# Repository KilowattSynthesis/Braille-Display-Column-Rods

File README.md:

# Braille-Display-Column-Rods
Braille display POC using tiny stepper motors to drive columns of the display

**Type 4 Braille Display**

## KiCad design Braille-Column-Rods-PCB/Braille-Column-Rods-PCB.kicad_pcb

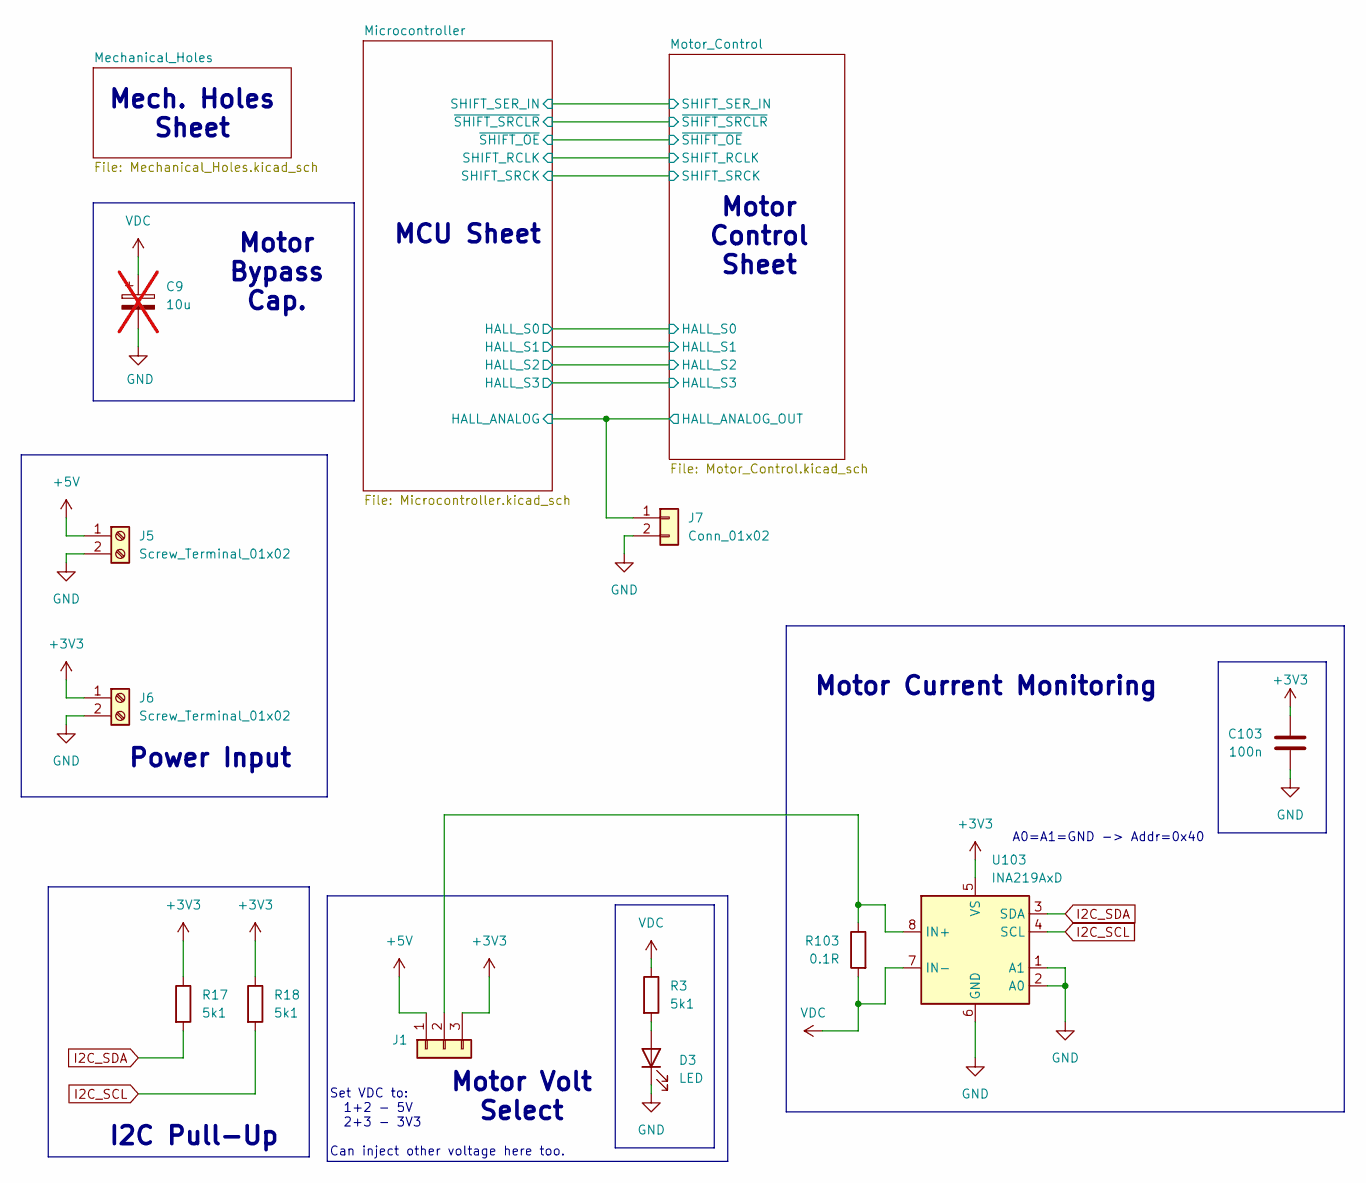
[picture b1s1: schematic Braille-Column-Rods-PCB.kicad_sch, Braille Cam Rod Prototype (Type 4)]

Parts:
C9: 10u; CP_Radial_D6.3mm_P2.50mm; not fitted
C103: 100n; C_0603_1608Metric_Pad1.08x0.95mm_HandSolder
D3: LED; LED_0603_1608Metric_Pad1.05x0.95mm_HandSolder
J1: Conn_01x03; PinHeader_1x03_P2.54mm_Vertical
J5, J6: Screw_Terminal_01x02; TerminalBlock_bornier-2_P5.08mm
J7: Conn_01x02; PinHeader_1x02_P2.54mm_Vertical
R3, R17, R18: 5k1; R_0603_1608Metric_Pad0.98x0.95mm_HandSolder
R103: 0.1R; R_1206_3216Metric_Pad1.30x1.75mm_HandSolder
U103: INA219AxD; SOIC-8_3.9x4.9mm_P1.27mm

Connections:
+3V3: C103.1, J1.3, J6.1, R17.1, R18.1, U103.5 (VS); also elsewhere on the board
+5V: J1.1, J5.1; also elsewhere on the board
/Microcontroller/HALL_ANALOG: J7.1; also elsewhere on the board
GND: C9.2, C103.2, D3.1 (K), J5.2, J6.2, J7.2, U103.1 (A1), U103.2 (A0), U103.6 (GND); also elsewhere on the board
I2C_SCL: R18.2, U103.4 (SCL); also elsewhere on the board
I2C_SDA: R17.2, U103.3 (SDA); also elsewhere on the board
unnamed: D3.2 (A), R3.2
unnamed: J1.2, R103.1, U103.8 (IN+)
VDC: C9.1, R3.1, R103.2, U103.7 (IN-); also elsewhere on the board

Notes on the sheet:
Motor Volt Select
Motor Bypass Cap.
A0=A1=GND -> Addr=0x40
Motor Current Monitoring
Mech. Holes Sheet
I2C Pull-Up
Set VDC to: 1+2 - 5V 2+3 - 3V3 Can inject other voltage here too.
MCU Sheet
Power Input
Motor Control Sheet

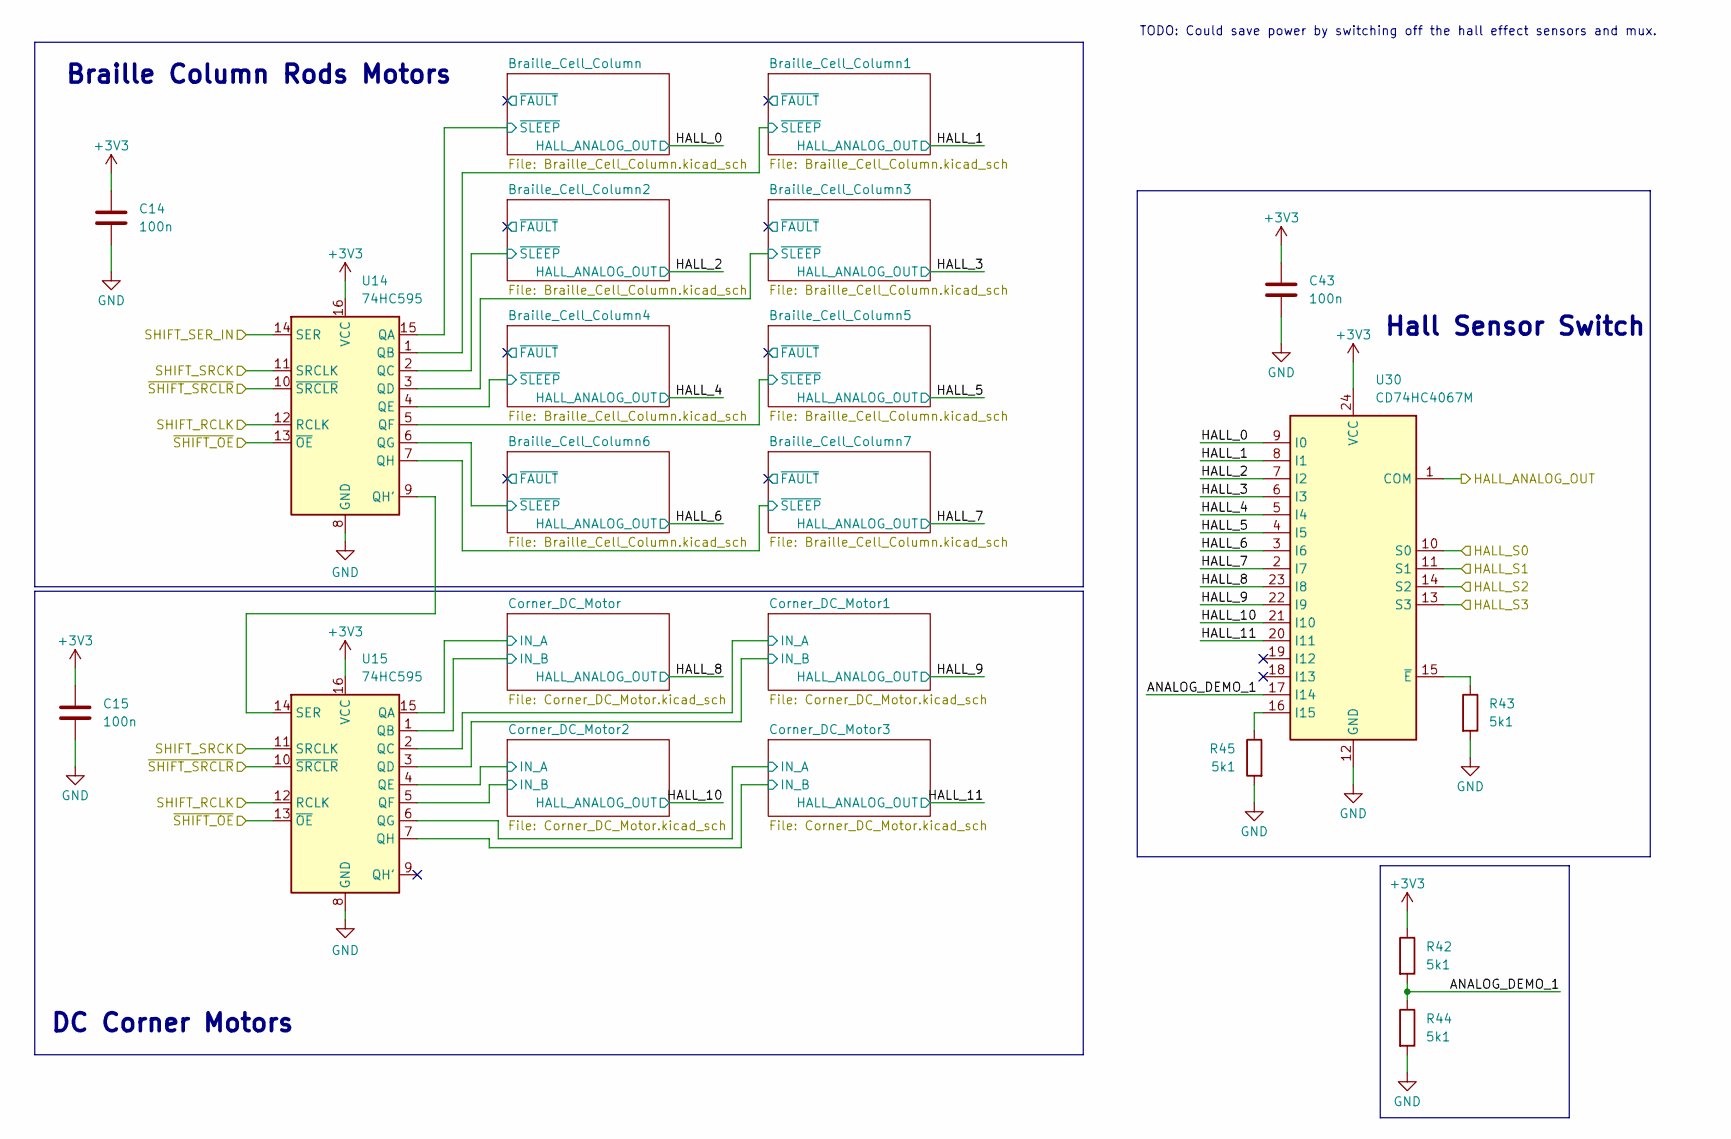
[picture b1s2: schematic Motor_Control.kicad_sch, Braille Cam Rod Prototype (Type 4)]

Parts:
C14, C15, C43: 100n; C_0603_1608Metric_Pad1.08x0.95mm_HandSolder
R42, R43, R44, R45: 5k1; R_0603_1608Metric_Pad0.98x0.95mm_HandSolder
U14, U15: 74HC595; SOP-16_3.9x9.9mm_P1.27mm; LCSC C5947
U30: CD74HC4067M; SOIC-24W_7.5x15.4mm_P1.27mm

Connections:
+3V3: C14.1, C15.1, C43.1, R42.1, U14.16 (VCC), U15.16 (VCC), U30.24 (VCC); also elsewhere on the board
/Microcontroller/HALL_ANALOG: U30.1 (COM); also elsewhere on the board
/Microcontroller/HALL_S0: U30.10 (S0); also elsewhere on the board
/Microcontroller/HALL_S1: U30.11 (S1); also elsewhere on the board
/Microcontroller/HALL_S2: U30.14 (S2); also elsewhere on the board
/Microcontroller/HALL_S3: U30.13 (S3); also elsewhere on the board
/Microcontroller/SHIFT_RCLK: U14.12 (RCLK), U15.12 (RCLK); also elsewhere on the board
/Microcontroller/SHIFT_SER_IN: U14.14 (SER); also elsewhere on the board
/Microcontroller/SHIFT_SRCK: U14.11 (SRCLK), U15.11 (SRCLK); also elsewhere on the board
/Microcontroller/~SHIFT_OE: U14.13 (~OE), U15.13 (~OE); also elsewhere on the board
/Microcontroller/~SHIFT_SRCLR: U14.10 (~SRCLR), U15.10 (~SRCLR); also elsewhere on the board
/Motor_Control/ANALOG_DEMO_1: R42.2, R44.1, U30.17 (I14)
/Motor_Control/Braille_Cell_Column1/~SLEEP: U14.1 (QB); also elsewhere on the board
/Motor_Control/Braille_Cell_Column2/~SLEEP: U14.2 (QC); also elsewhere on the board
/Motor_Control/Braille_Cell_Column3/~SLEEP: U14.3 (QD); also elsewhere on the board
/Motor_Control/Braille_Cell_Column4/~SLEEP: U14.4 (QE); also elsewhere on the board
/Motor_Control/Braille_Cell_Column5/~SLEEP: U14.5 (QF); also elsewhere on the board
/Motor_Control/Braille_Cell_Column6/~SLEEP: U14.6 (QG); also elsewhere on the board
/Motor_Control/Braille_Cell_Column7/~SLEEP: U14.7 (QH); also elsewhere on the board
/Motor_Control/Braille_Cell_Column/~SLEEP: U14.15 (QA); also elsewhere on the board
/Motor_Control/Corner_DC_Motor1/IN_A: U15.2 (QC); also elsewhere on the board
/Motor_Control/Corner_DC_Motor1/IN_B: U15.3 (QD); also elsewhere on the board
/Motor_Control/Corner_DC_Motor2/IN_A: U15.4 (QE); also elsewhere on the board
/Motor_Control/Corner_DC_Motor2/IN_B: U15.5 (QF); also elsewhere on the board
/Motor_Control/Corner_DC_Motor3/IN_A: U15.6 (QG); also elsewhere on the board
/Motor_Control/Corner_DC_Motor3/IN_B: U15.7 (QH); also elsewhere on the board
/Motor_Control/Corner_DC_Motor/IN_A: U15.15 (QA); also elsewhere on the board
/Motor_Control/Corner_DC_Motor/IN_B: U15.1 (QB); also elsewhere on the board
/Motor_Control/HALL_0: U30.9 (I0); also elsewhere on the board
/Motor_Control/HALL_1: U30.8 (I1); also elsewhere on the board
/Motor_Control/HALL_2: U30.7 (I2); also elsewhere on the board
/Motor_Control/HALL_3: U30.6 (I3); also elsewhere on the board
/Motor_Control/HALL_4: U30.5 (I4); also elsewhere on the board
/Motor_Control/HALL_5: U30.4 (I5); also elsewhere on the board
/Motor_Control/HALL_6: U30.3 (I6); also elsewhere on the board
/Motor_Control/HALL_7: U30.2 (I7); also elsewhere on the board
/Motor_Control/HALL_8: U30.23 (I8); also elsewhere on the board
/Motor_Control/HALL_9: U30.22 (I9); also elsewhere on the board
/Motor_Control/HALL_10: U30.21 (I10); also elsewhere on the board
/Motor_Control/HALL_11: U30.20 (I11); also elsewhere on the board
GND: C14.2, C15.2, C43.2, R43.2, R44.2, R45.2, U14.8 (GND), U15.8 (GND), U30.12 (GND); also elsewhere on the board
unnamed: U14.9 (QH'), U15.14 (SER)
unnamed: R45.1, U30.16 (I15)
unnamed: R43.1, U30.15 (~E)

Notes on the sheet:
Hall Sensor Switch
Braille Column Rods Motors
TODO: Could save power by switching off the hall effect sensors and mux.
DC Corner Motors

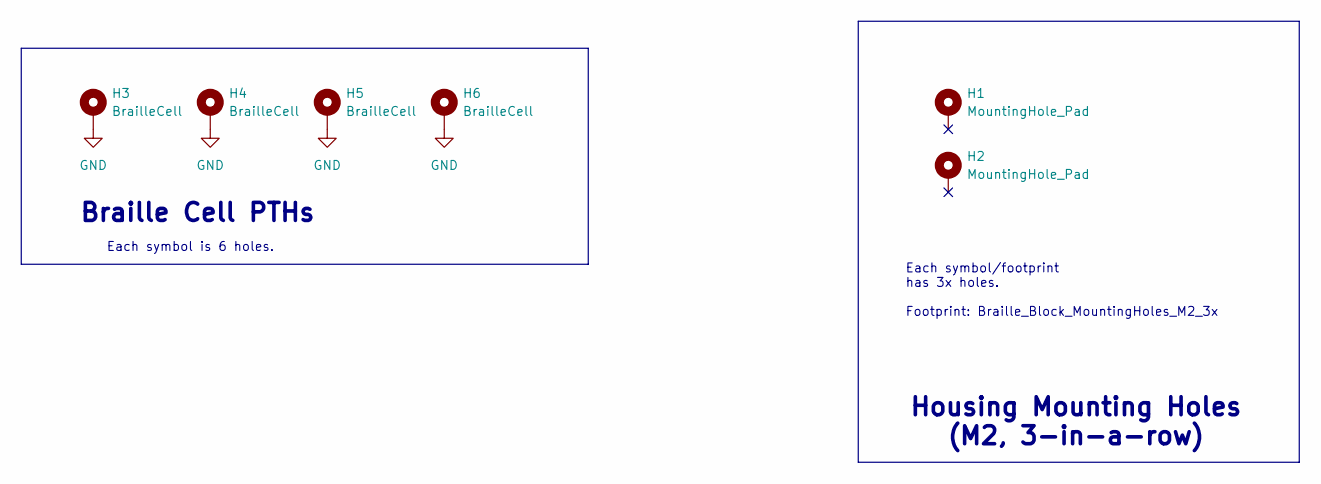
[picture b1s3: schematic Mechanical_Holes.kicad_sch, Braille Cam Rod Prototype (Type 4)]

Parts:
H1, H2: MountingHole_Pad; Braille_Block_MountingHoles_M2_3x
H3, H4, H5, H6: BrailleCell

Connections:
GND: H3.1, H4.1, H5.1, H6.1; also elsewhere on the board

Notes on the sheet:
Each symbol/footprint has 3x holes. Footprint: Braille_Block_MountingHoles_M2_3x
Housing Mounting Holes (M2, 3-in-a-row)
Braille Cell PTHs
Each symbol is 6 holes.

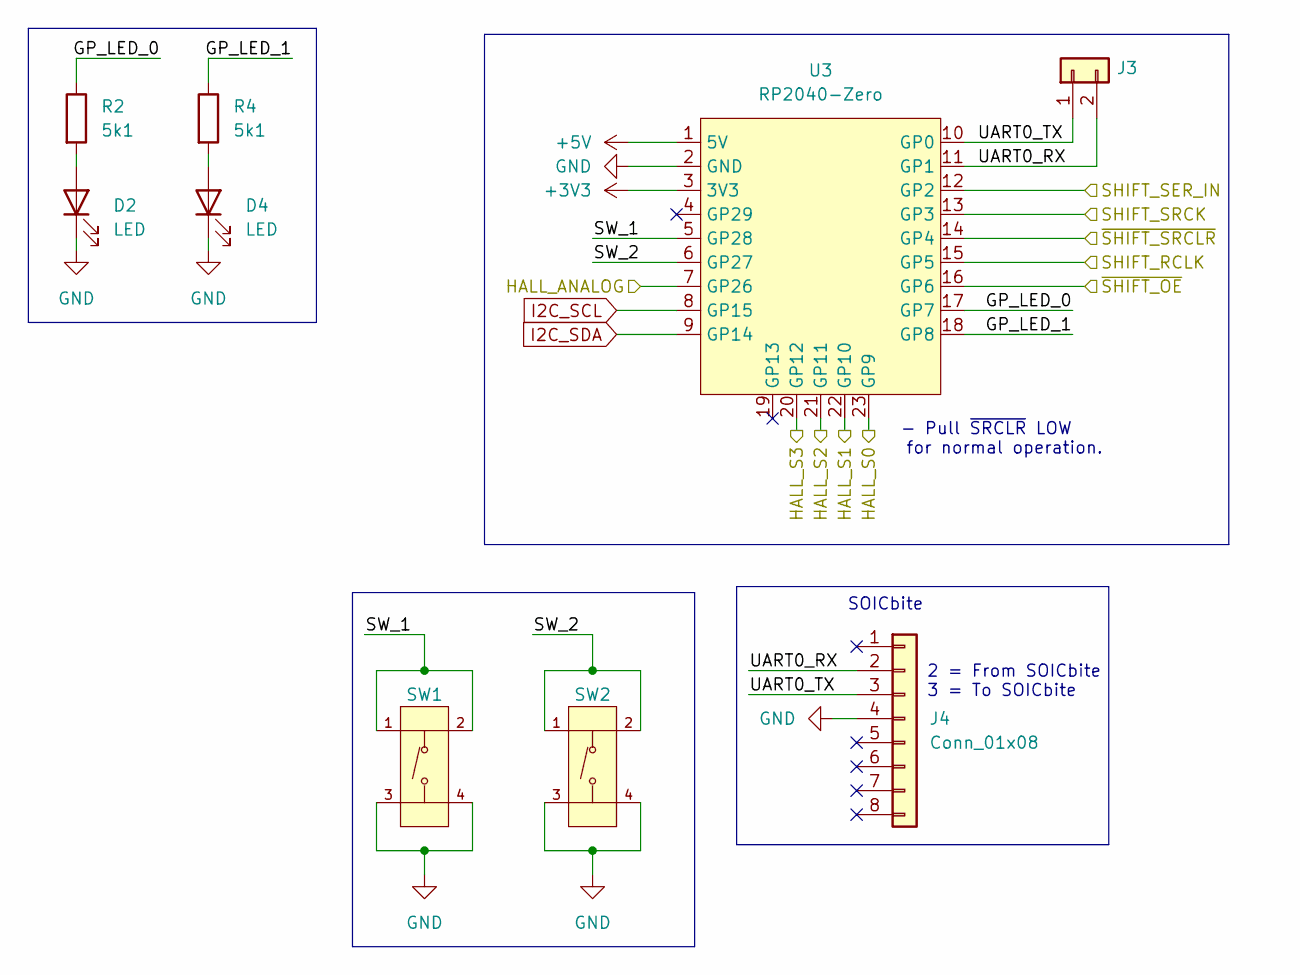
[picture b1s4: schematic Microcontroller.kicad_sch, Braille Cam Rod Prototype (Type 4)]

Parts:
D2, D4: LED; LED_0603_1608Metric_Pad1.05x0.95mm_HandSolder
J3: Conn_01x02; PinHeader_1x02_P2.54mm_Vertical
J4: Conn_01x08; SOICbite_clipProgSmall
R2, R4: 5k1; R_0603_1608Metric_Pad0.98x0.95mm_HandSolder
SW1, SW2: Tactile Button, 160gf; SW-SMD_4P-L5.1-W5.1-P3.70-LS6.5-TL-2; Voltage Rating (Dc) 12V; Part TS-1187A-B-A-B; LCSC C318884
U3: RP2040-Zero; RP2040 Zero

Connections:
+3V3: U3.3 (3V3); also elsewhere on the board
+5V: U3.1 (5V); also elsewhere on the board
/Microcontroller/GP_LED_0: R2.1, U3.17 (GP7)
/Microcontroller/GP_LED_1: R4.1, U3.18 (GP8)
/Microcontroller/HALL_ANALOG: U3.7 (GP26); also elsewhere on the board
/Microcontroller/HALL_S0: U3.23 (GP9); also elsewhere on the board
/Microcontroller/HALL_S1: U3.22 (GP10); also elsewhere on the board
/Microcontroller/HALL_S2: U3.21 (GP11); also elsewhere on the board
/Microcontroller/HALL_S3: U3.20 (GP12); also elsewhere on the board
/Microcontroller/SHIFT_RCLK: U3.15 (GP5); also elsewhere on the board
/Microcontroller/SHIFT_SER_IN: U3.12 (GP2); also elsewhere on the board
/Microcontroller/SHIFT_SRCK: U3.13 (GP3); also elsewhere on the board
/Microcontroller/SW_1: SW1.1 (A), SW1.2 (B), U3.5 (GP28)
/Microcontroller/SW_2: SW2.1 (A), SW2.2 (B), U3.6 (GP27)
/Microcontroller/UART0_RX: J3.2, J4.2, U3.11 (GP1)
/Microcontroller/UART0_TX: J3.1, J4.3, U3.10 (GP0)
/Microcontroller/~SHIFT_OE: U3.16 (GP6); also elsewhere on the board
/Microcontroller/~SHIFT_SRCLR: U3.14 (GP4); also elsewhere on the board
GND: D2.1 (K), D4.1 (K), J4.4, SW1.3 (C), SW1.4 (D), SW2.3 (C), SW2.4 (D), U3.2 (GND); also elsewhere on the board
I2C_SCL: U3.8 (GP15); also elsewhere on the board
I2C_SDA: U3.9 (GP14); also elsewhere on the board
unnamed: D2.2 (A), R2.2
unnamed: D4.2 (A), R4.2

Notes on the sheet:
SOICbite
2 = From SOICbite 3 = To SOICbite
- Pull ~{SRCLR} LOW for normal operation.

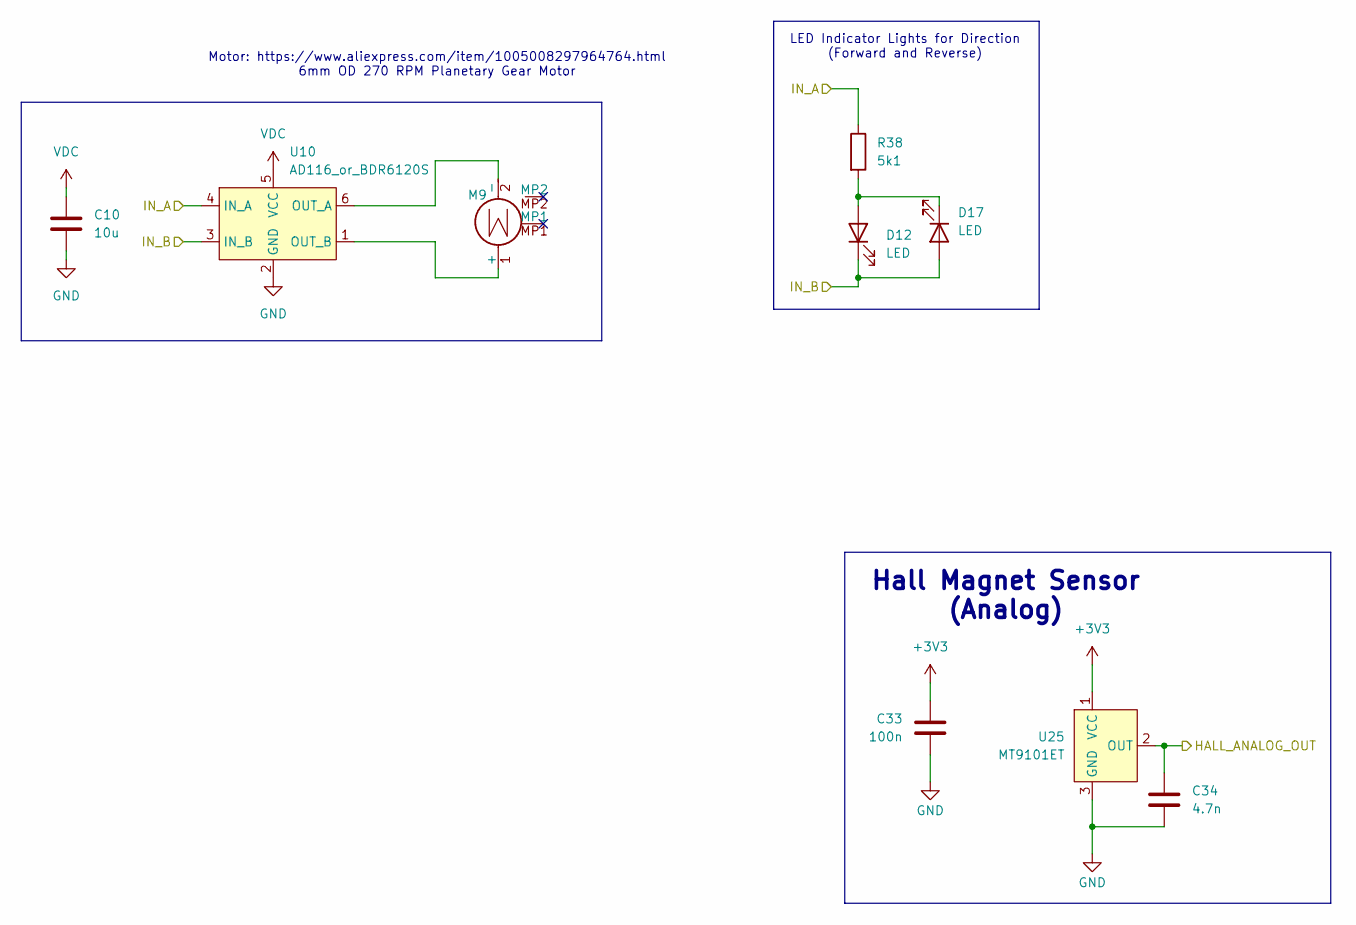
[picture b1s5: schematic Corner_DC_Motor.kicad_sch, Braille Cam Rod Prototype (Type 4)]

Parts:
C10: 10u; C_1206_3216Metric_Pad1.33x1.80mm_HandSolder
C33: 100n; C_0603_1608Metric_Pad1.08x0.95mm_HandSolder
C34: 4.7n; C_0603_1608Metric_Pad1.08x0.95mm_HandSolder
D12, D17: LED; LED_0603_1608Metric_Pad1.05x0.95mm_HandSolder
M9: Motor_DC_With_MP; DC_Motor_6mm_OD_with_3_Stage_Gearbox
R38: 5k1; R_0603_1608Metric_Pad0.98x0.95mm_HandSolder
U10: AD116_or_BDR6120S; SOT-23-6; LCSC C5455570
U25: MT9101ET; SOT-23-Hall; LCSC C2977713

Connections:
+3V3: C33.1, U25.1 (VCC); also elsewhere on the board
/Motor_Control/Corner_DC_Motor/IN_A: R38.1, U10.4 (IN_A); also elsewhere on the board
/Motor_Control/Corner_DC_Motor/IN_B: D12.1 (K), D17.2 (A), U10.3 (IN_B); also elsewhere on the board
/Motor_Control/HALL_8: C34.1, U25.2 (OUT); also elsewhere on the board
GND: C10.2, C33.2, C34.2, U10.2 (GND), U25.3 (GND); also elsewhere on the board
unnamed: D12.2 (A), D17.1 (K), R38.2
unnamed: M9.1 (+), U10.1 (OUT_B)
unnamed: M9.2 (-), U10.6 (OUT_A)
VDC: C10.1, U10.5 (VCC); also elsewhere on the board

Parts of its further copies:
C11, C12, C13: 10u; C_1206_3216Metric_Pad1.33x1.80mm_HandSolder
C35, C37, C39: 100n; C_0603_1608Metric_Pad1.08x0.95mm_HandSolder
C36, C38, C40: 4.7n; C_0603_1608Metric_Pad1.08x0.95mm_HandSolder
D13, D14, D15, D18, D19, D20: LED; LED_0603_1608Metric_Pad1.05x0.95mm_HandSolder
M10, M11, M12: Motor_DC_With_MP; DC_Motor_6mm_OD_with_3_Stage_Gearbox
R39, R40, R41: 5k1; R_0603_1608Metric_Pad0.98x0.95mm_HandSolder
U11, U12, U13: AD116_or_BDR6120S; SOT-23-6; LCSC C5455570
U26, U27, U28: MT9101ET; SOT-23-Hall; LCSC C2977713

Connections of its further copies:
+3V3: C35.1, C37.1, C39.1, U26.1 (VCC), U27.1 (VCC), U28.1 (VCC); also elsewhere on the board
/Motor_Control/Corner_DC_Motor1/IN_A: R39.1, U11.4 (IN_A); also elsewhere on the board
/Motor_Control/Corner_DC_Motor1/IN_B: D13.1 (K), D18.2 (A), U11.3 (IN_B); also elsewhere on the board
/Motor_Control/Corner_DC_Motor2/IN_A: R40.1, U12.4 (IN_A); also elsewhere on the board
/Motor_Control/Corner_DC_Motor2/IN_B: D14.1 (K), D19.2 (A), U12.3 (IN_B); also elsewhere on the board
/Motor_Control/Corner_DC_Motor3/IN_A: R41.1, U13.4 (IN_A); also elsewhere on the board
/Motor_Control/Corner_DC_Motor3/IN_B: D15.1 (K), D20.2 (A), U13.3 (IN_B); also elsewhere on the board
/Motor_Control/HALL_9: C36.1, U26.2 (OUT); also elsewhere on the board
/Motor_Control/HALL_10: C38.1, U27.2 (OUT); also elsewhere on the board
/Motor_Control/HALL_11: C40.1, U28.2 (OUT); also elsewhere on the board
GND: C11.2, C12.2, C13.2, C35.2, C36.2, C37.2, C38.2, C39.2, C40.2, U11.2 (GND), U12.2 (GND), U13.2 (GND), U26.3 (GND), U27.3 (GND), U28.3 (GND); also elsewhere on the board
unnamed: D13.2 (A), D18.1 (K), R39.2
unnamed: D14.2 (A), D19.1 (K), R40.2
unnamed: D15.2 (A), D20.1 (K), R41.2
unnamed: M10.1 (+), U11.1 (OUT_B)
unnamed: M10.2 (-), U11.6 (OUT_A)
unnamed: M11.1 (+), U12.1 (OUT_B)
unnamed: M11.2 (-), U12.6 (OUT_A)
unnamed: M12.1 (+), U13.1 (OUT_B)
unnamed: M12.2 (-), U13.6 (OUT_A)
VDC: C11.1, C12.1, C13.1, U11.5 (VCC), U12.5 (VCC), U13.5 (VCC); also elsewhere on the board

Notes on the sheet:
LED Indicator Lights for Direction (Forward and Reverse)
Hall Magnet Sensor (Analog)
Motor: https://www.aliexpress.com/item/1005008297964764.html 6mm OD 270 RPM Planetary Gear Motor

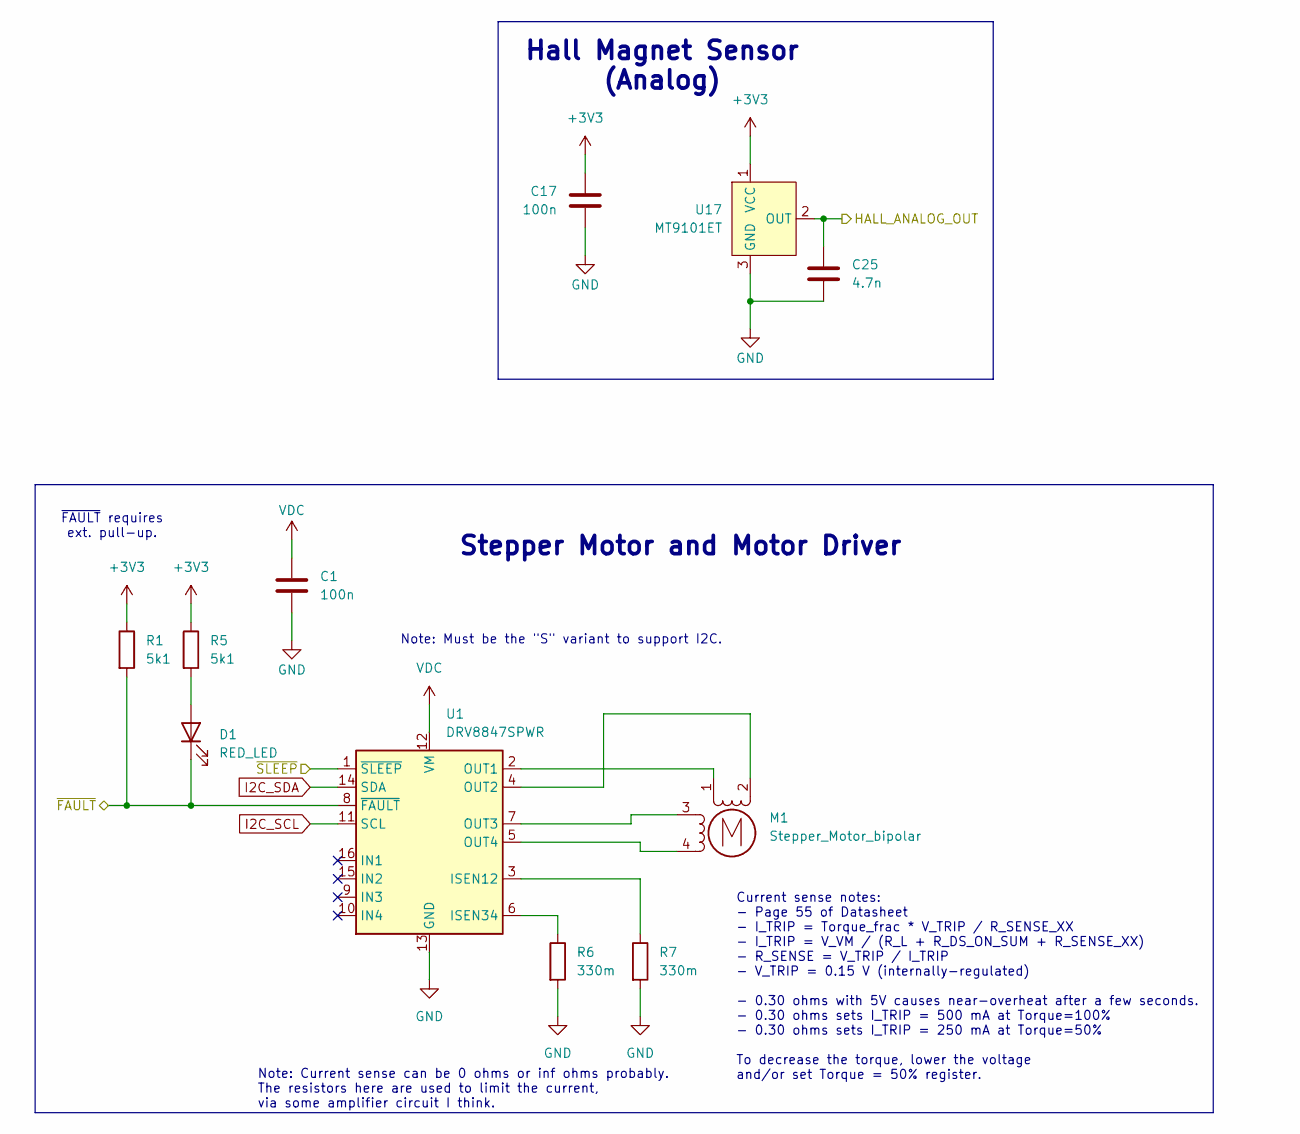
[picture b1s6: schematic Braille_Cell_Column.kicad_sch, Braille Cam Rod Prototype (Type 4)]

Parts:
C1, C17: 100n; C_0603_1608Metric_Pad1.08x0.95mm_HandSolder
C25: 4.7n; C_0603_1608Metric_Pad1.08x0.95mm_HandSolder
D1: RED_LED; LED_0603_1608Metric_Pad1.05x0.95mm_HandSolder
M1: Stepper_Motor_bipolar; MicroStepper_4.7_OD
R1, R5: 5k1; R_0603_1608Metric_Pad0.98x0.95mm_HandSolder
R6, R7: 330m; R_0603_1608Metric_Pad0.98x0.95mm_HandSolder
U1: DRV8847SPWR; TSSOP-16_4.4x5mm_P0.65mm
U17: MT9101ET; SOT-23-Hall; LCSC C2977713

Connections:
+3V3: C17.1, R1.1, R5.1, U17.1 (VCC); also elsewhere on the board
/Motor_Control/Braille_Cell_Column/~FAULT: D1.1 (K), R1.2, U1.8 (~FAULT)
/Motor_Control/Braille_Cell_Column/~SLEEP: U1.1 (~SLEEP); also elsewhere on the board
/Motor_Control/HALL_0: C25.1, U17.2 (OUT); also elsewhere on the board
GND: C1.2, C17.2, C25.2, R6.2, R7.2, U1.13 (GND), U17.3 (GND); also elsewhere on the board
I2C_SCL: U1.11 (SCL); also elsewhere on the board
I2C_SDA: U1.14 (SDA); also elsewhere on the board
unnamed: D1.2 (A), R5.2
unnamed: M1.2 (-), U1.4 (OUT2)
unnamed: R7.1, U1.3 (ISEN12)
unnamed: R6.1, U1.6 (ISEN34)
unnamed: M1.1, U1.2 (OUT1)
unnamed: M1.3, U1.7 (OUT3)
unnamed: M1.4, U1.5 (OUT4)
VDC: C1.1, U1.12 (VM); also elsewhere on the board

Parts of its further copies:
C2, C3, C4, C5, C6, C7, C8, C18, C19, C20, C21, C22, C23, C24: 100n; C_0603_1608Metric_Pad1.08x0.95mm_HandSolder
C26, C27, C28, C29, C30, C31, C32: 4.7n; C_0603_1608Metric_Pad1.08x0.95mm_HandSolder
D5, D6, D7, D8, D9, D10, D11: RED_LED; LED_0603_1608Metric_Pad1.05x0.95mm_HandSolder
M2, M3, M4, M5, M6, M7, M8: Stepper_Motor_bipolar; MicroStepper_4.7_OD
R8, R9, R12, R13, R16, R19, R22, R23, R26, R27, R30, R31, R34, R35: 5k1; R_0603_1608Metric_Pad0.98x0.95mm_HandSolder
R10, R11, R14, R15, R20, R21, R24, R25, R28, R29, R32, R33, R36, R37: 330m; R_0603_1608Metric_Pad0.98x0.95mm_HandSolder
U2, U4, U5, U6, U7, U8, U9: DRV8847SPWR; TSSOP-16_4.4x5mm_P0.65mm
U18, U19, U20, U21, U22, U23, U24: MT9101ET; SOT-23-Hall; LCSC C2977713

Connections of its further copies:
+3V3: C18.1, C19.1, C20.1, C21.1, C22.1, C23.1, C24.1, R8.1, R9.1, R12.1, R13.1, R16.1, R19.1, R22.1, R23.1, R26.1, R27.1, R30.1, R31.1, R34.1, R35.1, U18.1 (VCC), U19.1 (VCC), U20.1 (VCC), U21.1 (VCC), U22.1 (VCC), U23.1 (VCC), U24.1 (VCC); also elsewhere on the board
/Motor_Control/Braille_Cell_Column1/~FAULT: D5.1 (K), R8.2, U2.8 (~FAULT)
/Motor_Control/Braille_Cell_Column1/~SLEEP: U2.1 (~SLEEP); also elsewhere on the board
/Motor_Control/Braille_Cell_Column2/~FAULT: D6.1 (K), R12.2, U4.8 (~FAULT)
/Motor_Control/Braille_Cell_Column2/~SLEEP: U4.1 (~SLEEP); also elsewhere on the board
/Motor_Control/Braille_Cell_Column3/~FAULT: D7.1 (K), R16.2, U5.8 (~FAULT)
/Motor_Control/Braille_Cell_Column3/~SLEEP: U5.1 (~SLEEP); also elsewhere on the board
/Motor_Control/Braille_Cell_Column4/~FAULT: D8.1 (K), R22.2, U6.8 (~FAULT)
/Motor_Control/Braille_Cell_Column4/~SLEEP: U6.1 (~SLEEP); also elsewhere on the board
/Motor_Control/Braille_Cell_Column5/~FAULT: D9.1 (K), R26.2, U7.8 (~FAULT)
/Motor_Control/Braille_Cell_Column5/~SLEEP: U7.1 (~SLEEP); also elsewhere on the board
/Motor_Control/Braille_Cell_Column6/~FAULT: D10.1 (K), R30.2, U8.8 (~FAULT)
/Motor_Control/Braille_Cell_Column6/~SLEEP: U8.1 (~SLEEP); also elsewhere on the board
/Motor_Control/Braille_Cell_Column7/~FAULT: D11.1 (K), R34.2, U9.8 (~FAULT)
/Motor_Control/Braille_Cell_Column7/~SLEEP: U9.1 (~SLEEP); also elsewhere on the board
/Motor_Control/HALL_1: C26.1, U18.2 (OUT); also elsewhere on the board
/Motor_Control/HALL_2: C27.1, U19.2 (OUT); also elsewhere on the board
/Motor_Control/HALL_3: C28.1, U20.2 (OUT); also elsewhere on the board
/Motor_Control/HALL_4: C29.1, U21.2 (OUT); also elsewhere on the board
/Motor_Control/HALL_5: C30.1, U22.2 (OUT); also elsewhere on the board
/Motor_Control/HALL_6: C31.1, U23.2 (OUT); also elsewhere on the board
/Motor_Control/HALL_7: C32.1, U24.2 (OUT); also elsewhere on the board
GND: C2.2, C3.2, C4.2, C5.2, C6.2, C7.2, C8.2, C18.2, C19.2, C20.2, C21.2, C22.2, C23.2, C24.2, C26.2, C27.2, C28.2, C29.2, C30.2, C31.2, C32.2, R10.2, R11.2, R14.2, R15.2, R20.2, R21.2, R24.2, R25.2, R28.2, R29.2, R32.2, R33.2, R36.2, R37.2, U2.13 (GND), U4.13 (GND), U5.13 (GND), U6.13 (GND), U7.13 (GND), U8.13 (GND), U9.13 (GND), U18.3 (GND), U19.3 (GND), U20.3 (GND), U21.3 (GND), U22.3 (GND), U23.3 (GND), U24.3 (GND); also elsewhere on the board
I2C_SCL: U2.11 (SCL), U4.11 (SCL), U5.11 (SCL), U6.11 (SCL), U7.11 (SCL), U8.11 (SCL), U9.11 (SCL); also elsewhere on the board
I2C_SDA: U2.14 (SDA), U4.14 (SDA), U5.14 (SDA), U6.14 (SDA), U7.14 (SDA), U8.14 (SDA), U9.14 (SDA); also elsewhere on the board
unnamed: D5.2 (A), R9.2
unnamed: D6.2 (A), R13.2
unnamed: D7.2 (A), R19.2
unnamed: D8.2 (A), R23.2
unnamed: D9.2 (A), R27.2
unnamed: D10.2 (A), R31.2
unnamed: D11.2 (A), R35.2
unnamed: M2.2 (-), U2.4 (OUT2)
unnamed: M3.2 (-), U4.4 (OUT2)
unnamed: M4.2 (-), U5.4 (OUT2)
unnamed: M5.2 (-), U6.4 (OUT2)
unnamed: M6.2 (-), U7.4 (OUT2)
unnamed: M7.2 (-), U8.4 (OUT2)
unnamed: M8.2 (-), U9.4 (OUT2)
unnamed: R11.1, U2.3 (ISEN12)
unnamed: R10.1, U2.6 (ISEN34)
unnamed: M2.1, U2.2 (OUT1)
unnamed: M2.3, U2.7 (OUT3)
unnamed: M2.4, U2.5 (OUT4)
unnamed: R15.1, U4.3 (ISEN12)
unnamed: R14.1, U4.6 (ISEN34)
unnamed: M3.1, U4.2 (OUT1)
unnamed: M3.3, U4.7 (OUT3)
unnamed: M3.4, U4.5 (OUT4)
unnamed: R21.1, U5.3 (ISEN12)
unnamed: R20.1, U5.6 (ISEN34)
unnamed: M4.1, U5.2 (OUT1)
unnamed: M4.3, U5.7 (OUT3)
unnamed: M4.4, U5.5 (OUT4)
unnamed: R25.1, U6.3 (ISEN12)
unnamed: R24.1, U6.6 (ISEN34)
unnamed: M5.1, U6.2 (OUT1)
unnamed: M5.3, U6.7 (OUT3)
unnamed: M5.4, U6.5 (OUT4)
unnamed: R29.1, U7.3 (ISEN12)
unnamed: R28.1, U7.6 (ISEN34)
unnamed: M6.1, U7.2 (OUT1)
unnamed: M6.3, U7.7 (OUT3)
unnamed: M6.4, U7.5 (OUT4)
unnamed: R33.1, U8.3 (ISEN12)
unnamed: R32.1, U8.6 (ISEN34)
unnamed: M7.1, U8.2 (OUT1)
unnamed: M7.3, U8.7 (OUT3)
unnamed: M7.4, U8.5 (OUT4)
unnamed: R37.1, U9.3 (ISEN12)
unnamed: R36.1, U9.6 (ISEN34)
unnamed: M8.1, U9.2 (OUT1)
unnamed: M8.3, U9.7 (OUT3)
unnamed: M8.4, U9.5 (OUT4)
VDC: C2.1, C3.1, C4.1, C5.1, C6.1, C7.1, C8.1, U2.12 (VM), U4.12 (VM), U5.12 (VM), U6.12 (VM), U7.12 (VM), U8.12 (VM), U9.12 (VM); also elsewhere on the board

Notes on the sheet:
Note: Current sense can be 0 ohms or inf ohms probably. The resistors here are used to limit the current, via some amplifier circuit I think.
Current sense notes: - Page 55 of Datasheet - I_TRIP = Torque_frac * V_TRIP / R_SENSE_XX - I_TRIP = V_VM / (R_L + R_DS_ON_SUM + R_SENSE_XX) - R_SENSE = V_TRIP / I_TRIP - V_TRIP = 0.15 V (internally-regulated) - 0.30 ohms with 5V causes near-overheat after a few seconds. - 0.30 ohms sets I_TRIP = 50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
~{FAULT} requires ext. pull-up.
Note: Must be the "S" variant to support I2C.
Stepper Motor and Motor Driver
Hall Magnet Sensor (Analog)

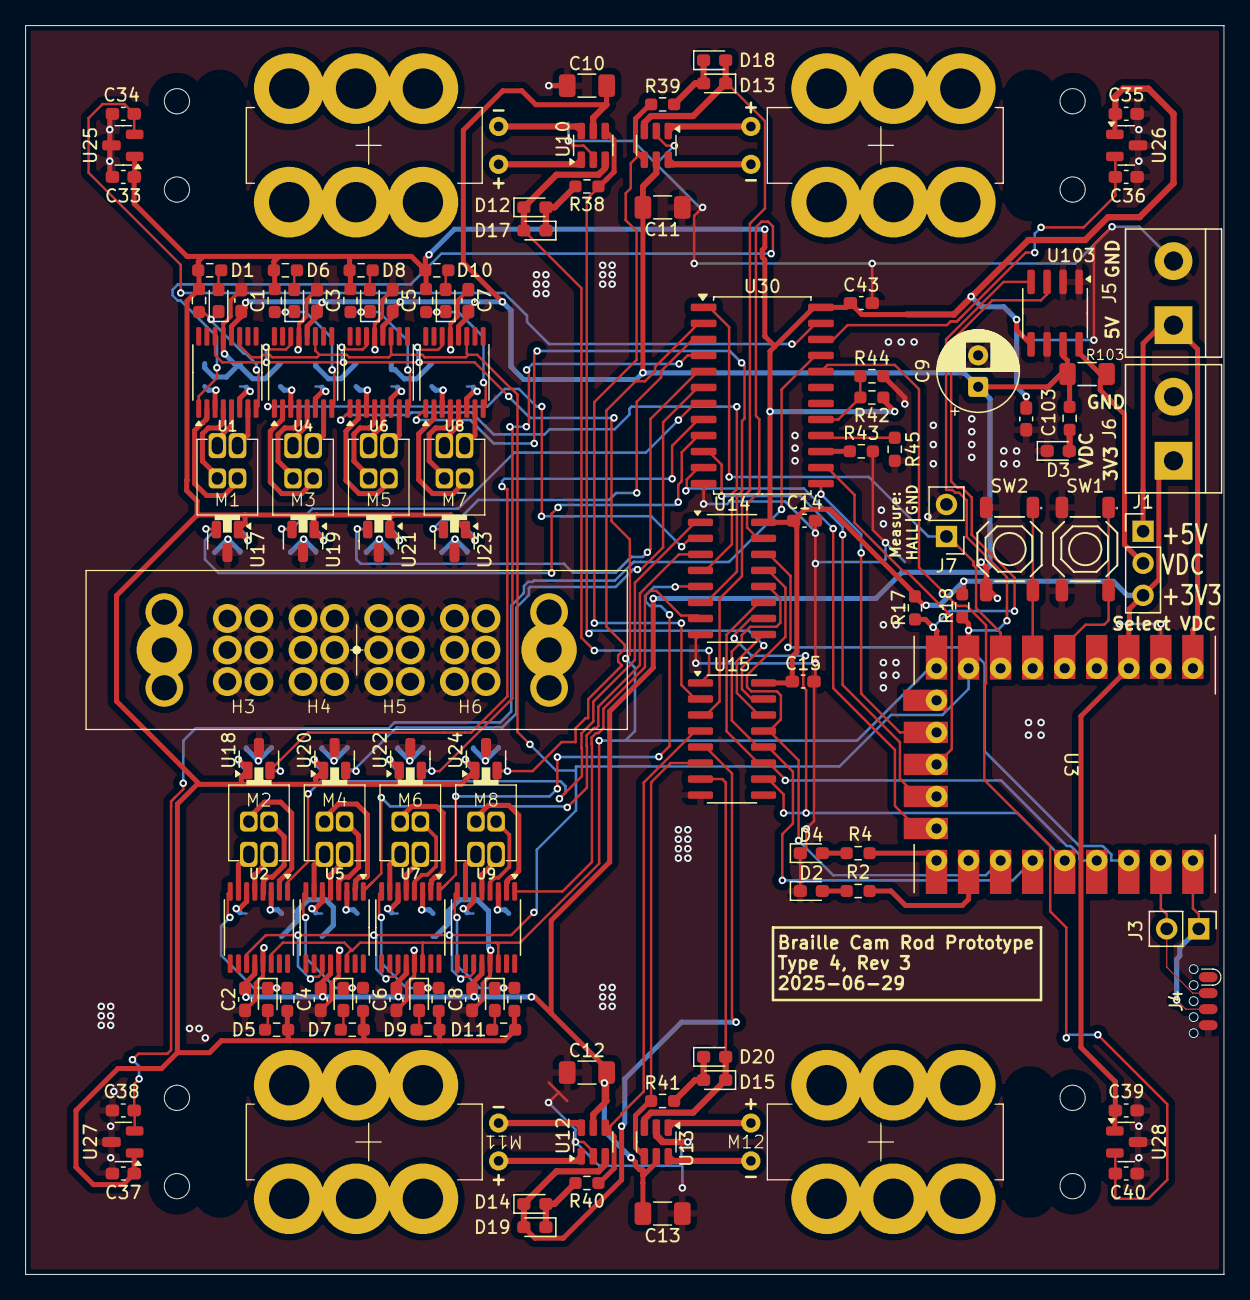
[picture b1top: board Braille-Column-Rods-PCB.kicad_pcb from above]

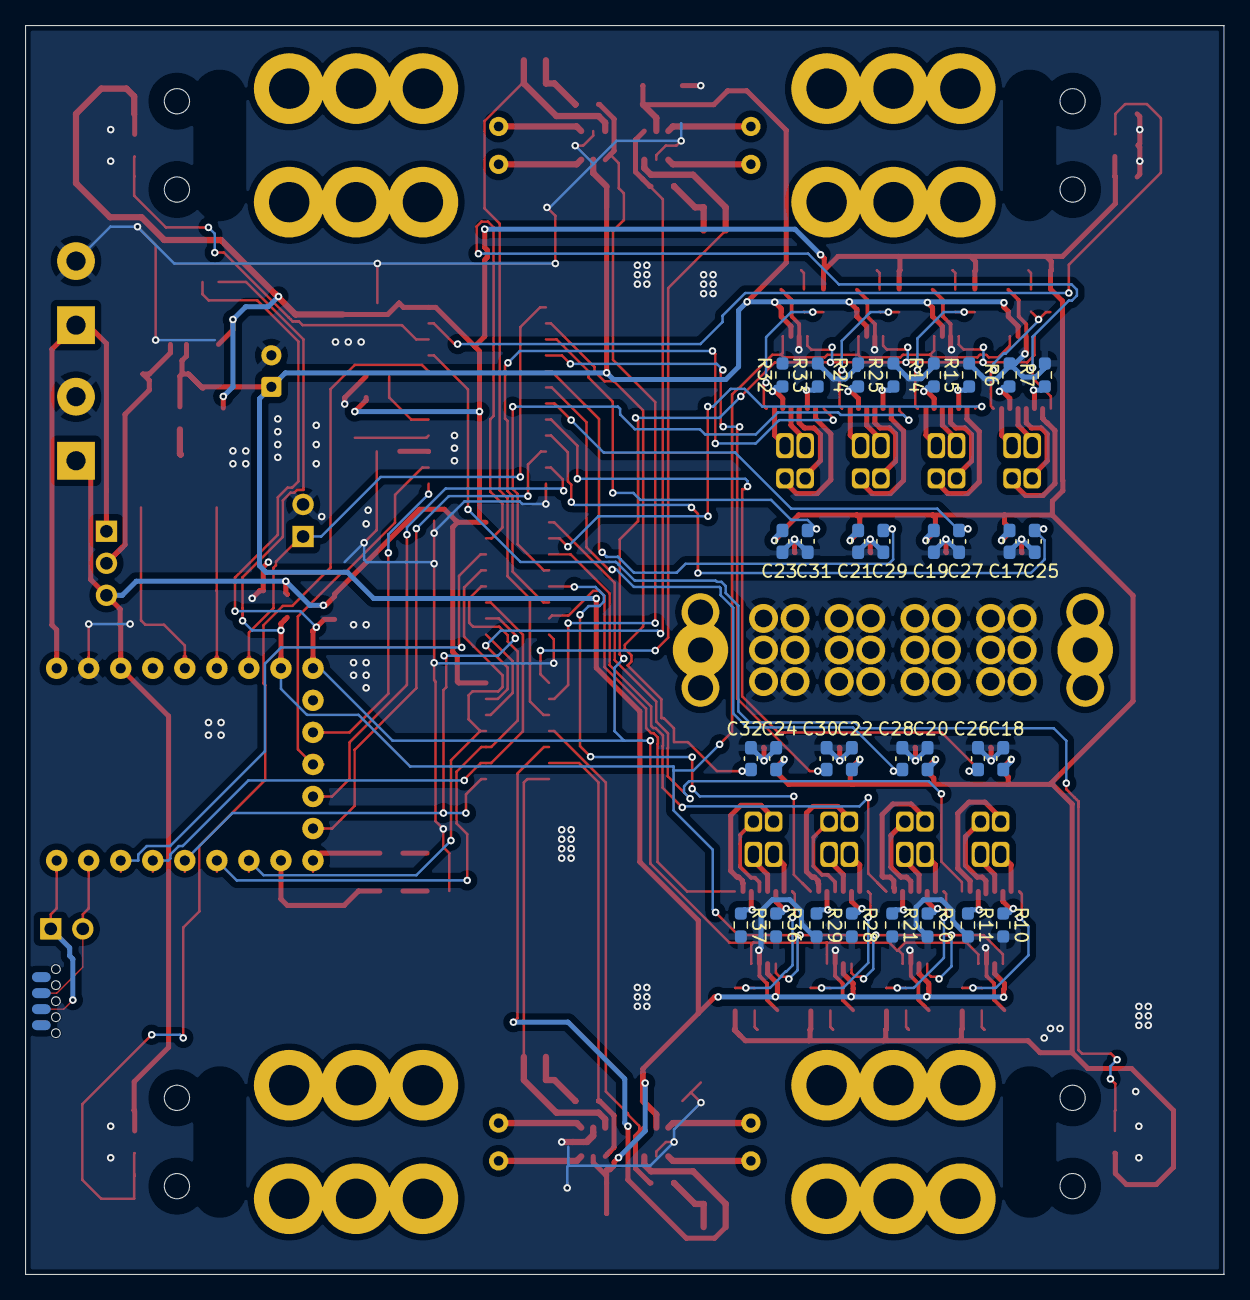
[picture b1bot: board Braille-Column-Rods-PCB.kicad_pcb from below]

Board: 2 copper layers, 95.0 x 99.0 mm, 161 parts (32 on the bottom side), 134 nets.

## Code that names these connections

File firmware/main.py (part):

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SHIFT_REGISTER_SLEEP_US = 100

# Pin definitions for shift register control
PIN_SHIFT_SER_IN = Pin(2, Pin.OUT)  # GP2: Serial data input
PIN_SHIFT_SRCK = Pin(3, Pin.OUT)  # GP3: Shift register clock
PIN_SHIFT_N_SRCLR = Pin(4, Pin.OUT)  # GP4: Shift register clear
PIN_SHIFT_RCLK = Pin(5, Pin.OUT)  # GP5: Register clock (latch)
PIN_SHIFT_N_OE = Pin(6, Pin.OUT)  # GP6: Output enable

# Pin definitions for general purpose LEDs and switches.
PIN_SW1 = Pin(28, Pin.IN, Pin.PULL_UP)
PIN_SW2 = Pin(27, Pin.IN, Pin.PULL_UP)
PIN_GP_LED_0 = Pin(7, Pin.OUT)
PIN_GP_LED_1 = Pin(8, Pin.OUT)

# Pin definitions for hall sensor control (mux and ADC).
PIN_HALL_SELECT_0 = Pin(9, Pin.OUT)
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    time.sleep_ms(SHIFT_REGISTER_INIT_SLEEP_MS)

    PIN_SHIFT_N_OE.value(0)  # Active low, set low to enable outputs
    PIN_SHIFT_SRCK.value(0)  # Clock starts low
    PIN_SHIFT_RCLK.value(0)  # Latch starts low

    # Wait for initialization to complete
    time.sleep_ms(SHIFT_REGISTER_INIT_SLEEP_MS)
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    # Shift out all 16 bits
    for bit in reversed(data):  # Shift MSB first
        # Set data bit.
        PIN_SHIFT_SER_IN.value(1 if bit else 0)
        time.sleep_us(SHIFT_REGISTER_SLEEP_US)

        # Clock in the bit.
        PIN_SHIFT_SRCK.value(1)
        time.sleep_us(SHIFT_REGISTER_SLEEP_US)
        PIN_SHIFT_SRCK.value(0)
        time.sleep_us(SHIFT_REGISTER_SLEEP_US)

    # Latch the data to outputs
    PIN_SHIFT_RCLK.value(1)
    time.sleep_us(SHIFT_REGISTER_SLEEP_US)
    PIN_SHIFT_RCLK.value(0)
    time.sleep_us(SHIFT_REGISTER_SLEEP_US)


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def demo_gp_leds() -> None:
    """Demo the general purpose LEDs."""
    for i in range(2):
        PIN_GP_LED_0.value(0)
        PIN_GP_LED_1.value(1)
        time.sleep_ms(100)
        PIN_GP_LED_0.value(1)
        PIN_GP_LED_1.value(0)
        time.sleep_ms(100)

    PIN_GP_LED_0.value(0)
    PIN_GP_LED_1.value(0)


def demo_zeroing_corner_motor(corner_number: int) -> None:
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def main() -> None:
    print("Starting init.")
    init_shift_register()
    PIN_GP_LED_0.value(0)
    PIN_GP_LED_1.value(0)

    init_hall_sensor()
    print("Init complete.")
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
